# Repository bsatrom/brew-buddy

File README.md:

# Brew Buddy

Source for the BrewBuddy project. Contains sources for board hardware/layout, firmware and a 3d printed enclosure.

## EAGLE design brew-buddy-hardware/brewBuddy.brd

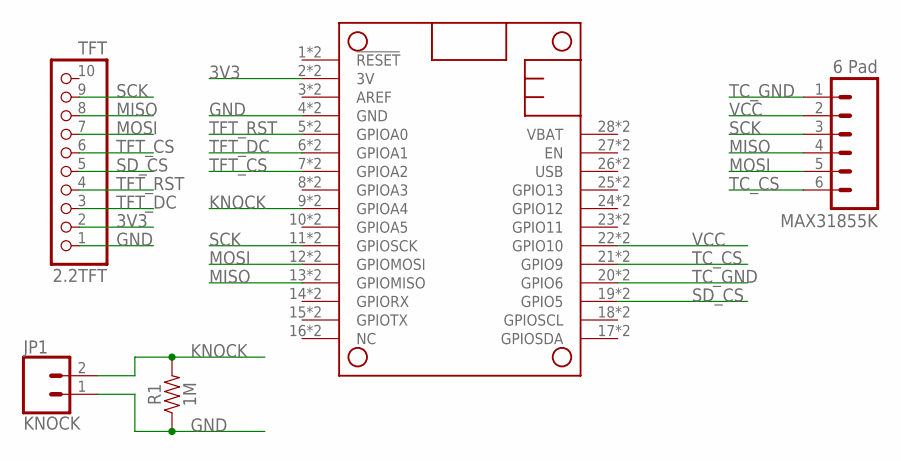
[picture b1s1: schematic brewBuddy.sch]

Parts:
2.2TFT: TFT; MICROBUILDER_1X10_ROUND_2MM
JP1: KNOCK; SCREWTERMINAL-5MM-2
MAX31855K: 6 Pad; 1X06_LONGPADS
MS1: FEATHERWING_SMTDUAL; FEATHERWING_SMT2
R1: 1M; 0805

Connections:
3V3: 2.2TFT.2, MS1.2 (3V), MS1.2' (3V)
GND: 2.2TFT.1, JP1.1, MS1.4 (GND), MS1.4' (GND), R1.1
KNOCK: JP1.2, MS1.9 (GPIOA4), MS1.9' (GPIOA4), R1.2
MISO: 2.2TFT.8, MAX31855K.4, MS1.13 (GPIOMISO), MS1.13' (GPIOMISO)
MOSI: 2.2TFT.7, MAX31855K.5, MS1.12 (GPIOMOSI), MS1.12' (GPIOMOSI)
SCK: 2.2TFT.9, MAX31855K.3, MS1.11 (GPIOSCK), MS1.11' (GPIOSCK)
SD_CS: 2.2TFT.5, MS1.19 (GPIO5), MS1.19' (GPIO5)
TC_CS: MAX31855K.6, MS1.21 (GPIO9), MS1.21' (GPIO9)
TC_GND: MAX31855K.1, MS1.20 (GPIO6), MS1.20' (GPIO6)
TFT_CS: 2.2TFT.6, MS1.7 (GPIOA2), MS1.7' (GPIOA2)
TFT_DC: 2.2TFT.3, MS1.6 (GPIOA1), MS1.6' (GPIOA1)
TFT_RST: 2.2TFT.4, MS1.5 (GPIOA0), MS1.5' (GPIOA0)
VCC: MAX31855K.2, MS1.22 (GPIO10), MS1.22' (GPIO10)

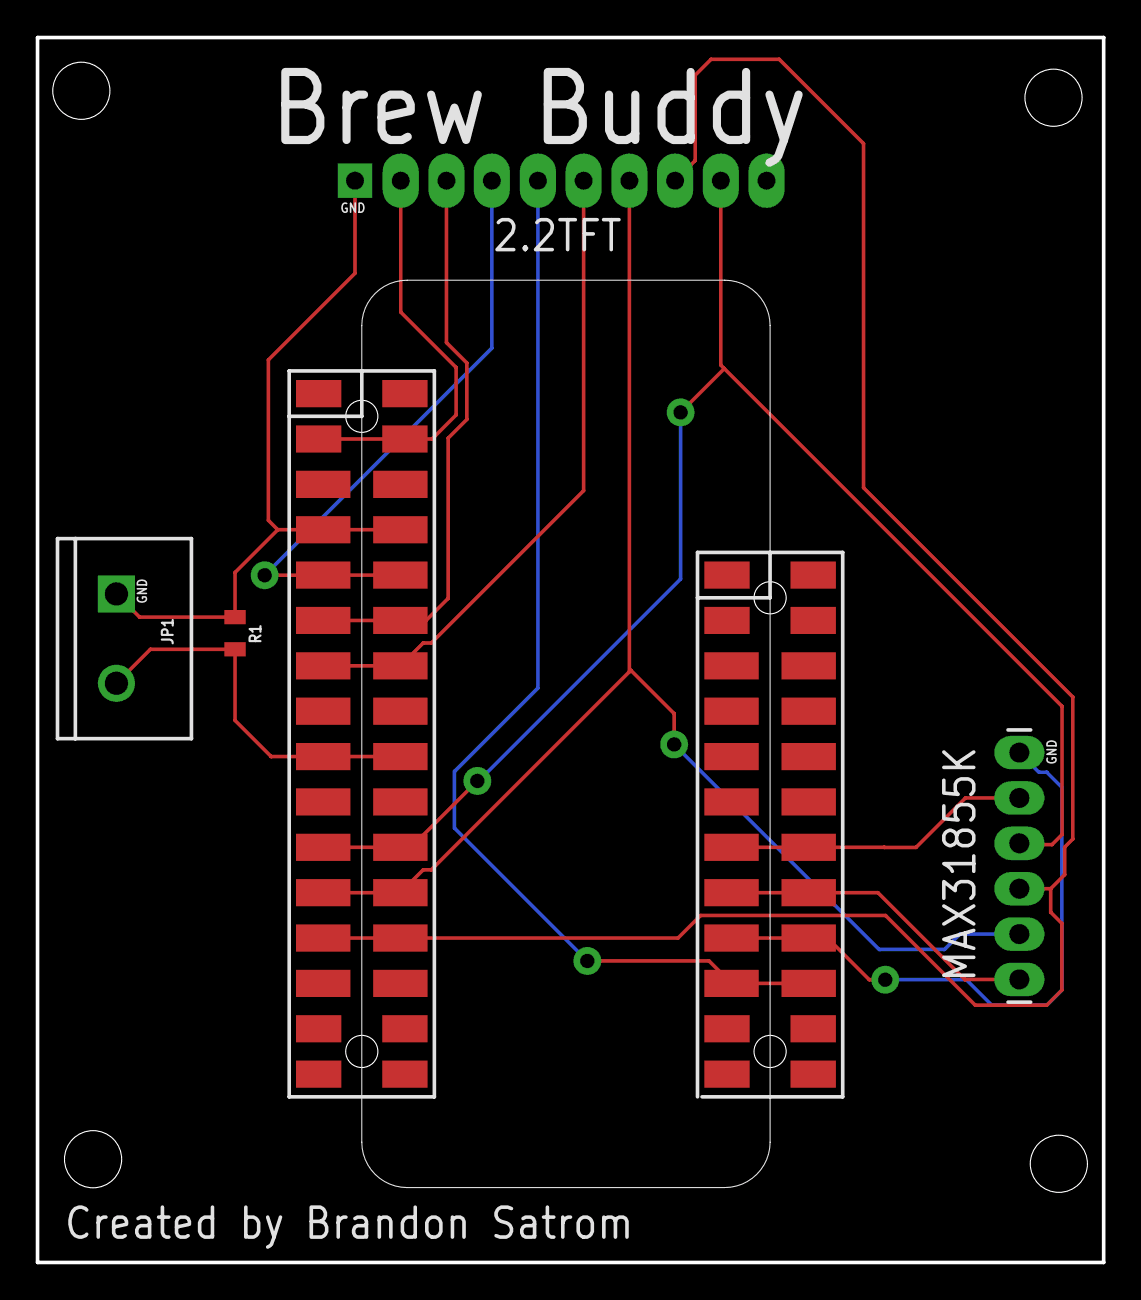
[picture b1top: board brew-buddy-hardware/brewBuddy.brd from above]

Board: 2 copper layers, 59.7 x 68.6 mm, 5 parts (0 on the bottom side), 13 nets.

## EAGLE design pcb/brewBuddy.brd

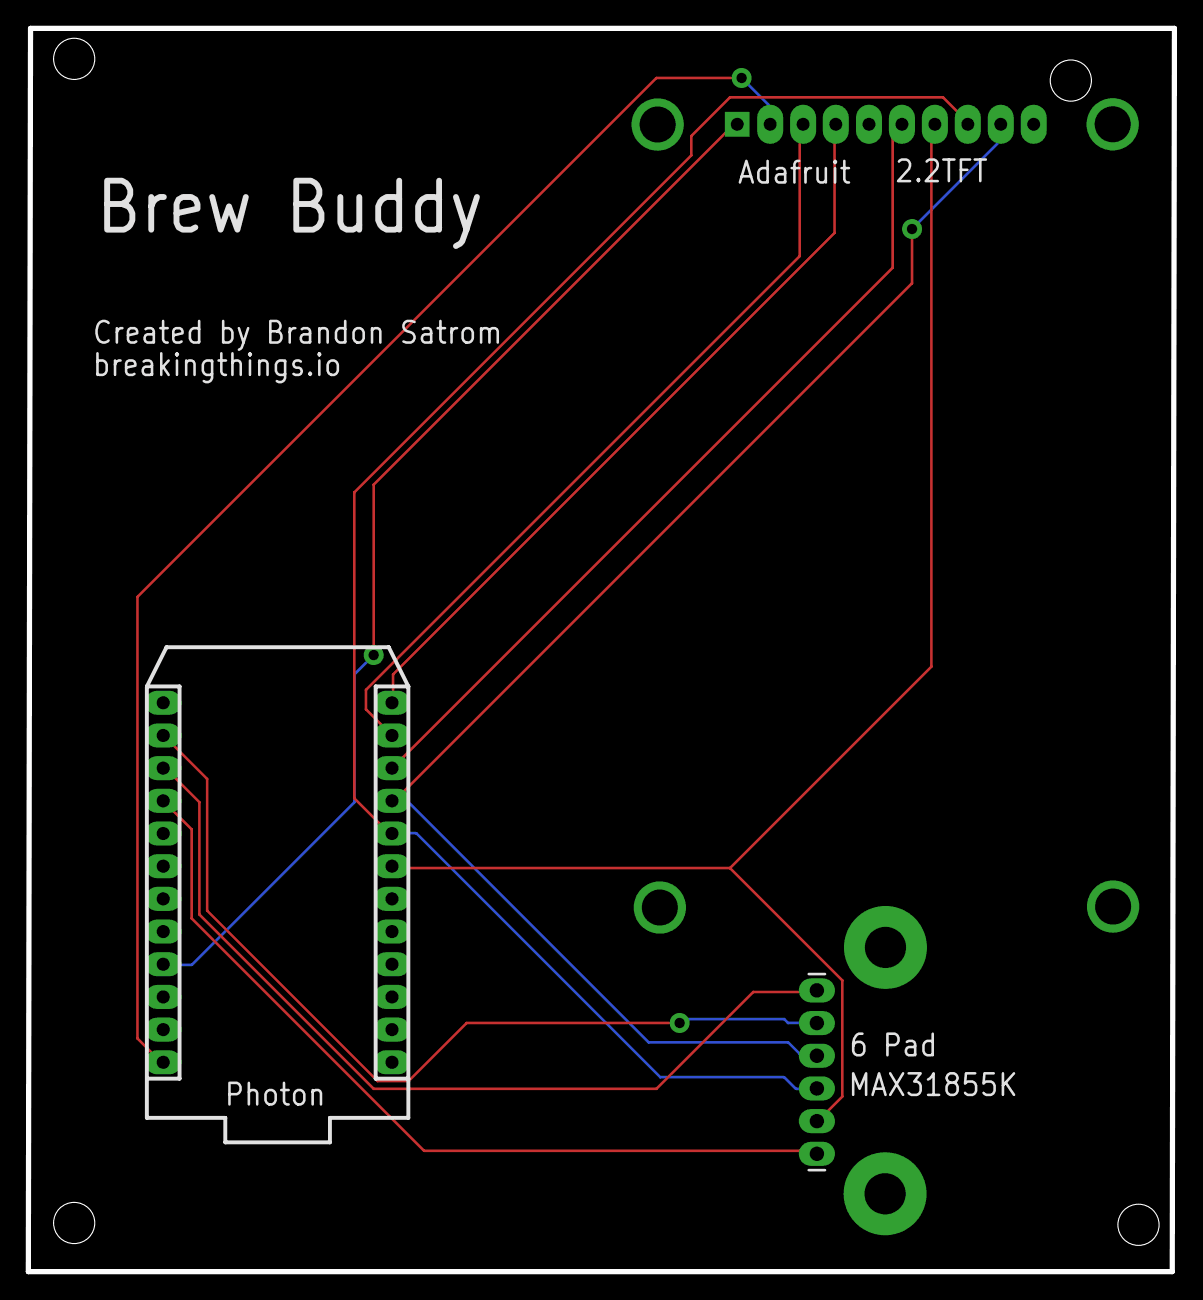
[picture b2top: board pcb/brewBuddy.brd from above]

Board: 2 copper layers, 89.1 x 96.6 mm, 3 parts (0 on the bottom side), 11 nets.

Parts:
2.2TFT: MICROBUILDER_1X10_ROUND_2MM
MAX31855K: 6 Pad; 1X06_LONGPADS
U$1: PHOTON_WITH_HEADERS; PHOTON

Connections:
unnamed: MAX31855K.1, U$1.15
unnamed: MAX31855K.2, U$1.14
unnamed: MAX31855K.6, U$1.16
unnamed: 2.2TFT.9, MAX31855K.3, U$1.9
unnamed: 2.2TFT.8, MAX31855K.4, U$1.8
unnamed: 2.2TFT.7, MAX31855K.5, U$1.7
unnamed: 2.2TFT.6, U$1.10
unnamed: 2.2TFT.4, U$1.12
unnamed: 2.2TFT.3, U$1.11
unnamed: 2.2TFT.2, U$1.24
unnamed: 2.2TFT.1, U$1.21

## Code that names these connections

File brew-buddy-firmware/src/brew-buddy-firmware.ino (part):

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SparkFunMAX31855k probe(CHIP_SELECT_PIN, VCC, GND);

// CS Pin for SD Card on TFT
#define SD_CS D2
#define TFT_CS A2
#define TFT_DC A1
#define TFT_RST A0
// Use hardware SPI
// cs = A2, dc = A1, rst = A0
Adafruit_ILI9341 tft = Adafruit_ILI9341(TFT_CS, TFT_DC, TFT_RST);
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
// #include "bmpDraw.h"

// Knock sensor pin
const uint8_t KNOCK_PIN = A4;

// Timing Variables
unsigned long previousTempMillis = 0;
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  Serial.begin(9600);
  deviceID = System.deviceID();

  pinMode(KNOCK_PIN, INPUT_PULLDOWN);

  //Particle Variables
  Particle.variable("brewStage", brewStage);
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
  if (isFermentationMode)
  {
    int16_t knockVal = analogRead(KNOCK_PIN) / 16;

    if (knockVal >= 6)
    {
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    printSubheadingLine("Waiting for");
    printSubheadingLine("Fermentation...");

    System.sleep(KNOCK_PIN, CHANGE);

    return 1;
  }
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
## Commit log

2016-01-06 resolve .gitignore conflict
2016-01-06 added backend posting and counter on TFT
2016-01-06 added heading text for temp and counter
2016-01-06 Added to Readme
2016-01-06 removed Arduino example/test code
2016-01-07 added temp graph to bottom of TFT
2016-01-21 added Eagle files for brew-buddy PCB
2016-03-17 added Eagle files
2016-07-12 updated brd with larger pads for othermill
2016-07-14 widened wires for cnc millin
2016-07-18 updated brd for othermill
2016-07-20 moved traces to bottom layer for othermill
2016-07-20 added BB name to board
2016-09-06 modified BRD to make room for components
2016-09-07 additional BRD mods
2016-10-27 added enclosure files
2016-10-27 added supports
2016-10-27 updated snclosure with tweaks
2016-10-30 tweaked enclosure (v3)
2016-10-30 additional enclosure tweaks (v4)
2016-10-31 designed top of enclosure
2016-10-31 tweaked top enclosure
2016-11-08 modified sketch to show image on startup; tweaked pcb
2016-11-10 moved WebHook to Firebase; added support for multiple commands in brew creation
2016-11-10 added line to free char memory after processing
2016-11-29 updated enclosure design for smaller case
2016-11-29 added enclosure STL
2016-11-30 modified top of enclosure design
2017-01-08 modified BB firmware to fix a few bugs
2017-01-12 tweaked display settings and location for temp graph
2017-02-13 added basic simulation support
2017-02-13 remove node_modulues
2017-02-13 add node_modulus to `.gitignore`
2017-02-13 cleaned up status changes
2017-02-20 add temp simulator object to control pattern
2017-02-21 cleanup refactor
2019-02-12 re-org and cleanup repo for 2.0 project
2019-02-12 updated library refs; closes #1
2019-02-12 change pin mappings for Argon; closes #2; closes #3
2019-02-20 updated schematic and board for Argon
2019-02-20 completed sd card support; closes #4; closes #5
2019-02-21 overlay text on image for splash; closes #12
2019-02-21 clear screen after startup; closes #16
2019-02-21 up SPI TFT frequency to 120 MHz; closes #11
2019-02-21 implement System threading; closes #17
2019-02-21 added modes for brew and fermentation; closes #8
2019-02-21 calibrate knock sensor; closes #7
2019-02-21 Set up CI with Azure Pipelines
2019-02-21 Update azure-pipelines.yml for Azure Pipelines
2019-02-22 update dependencies for cloud build
2019-02-22 Update azure-pipelines.yml for Azure Pipelines
    Added saveTo command for firmware build
2019-02-22 Update azure-pipelines.yml for Azure Pipelines
    Ad]d GitHub release task
2019-02-22 added brew bitmap
2019-02-22 implemented sleep mode with Knock sensor; closes #10
2019-02-26 added fermentation variables; closes #21
2019-02-26 added fermentation rate logic; closes #23
2019-02-28 separate readings from posting; closes #18; closes #24
2019-02-28 clean-up tempo monitoring posts; closes #22
2019-03-04 display fermentation time; closes #29
2019-03-04 give all pubs a common root; closes #30
2019-03-08 publish temp and fermentation rates; closes #31
2019-03-12 add batt check logic and low batt notification; closes #38; closes #35
2019-03-13 tweak clear screen to leave top bar pixels alone; closes #39
2019-03-13 Add voltage check function and clean up top bar clearing; closes #41
2019-03-13 clean up fermentation display; closes #42
2019-03-14 get MQTT with AzIoT working; for #37
2019-03-16 continue work on Azure IoT Hub integration
2019-03-20 completed c2d message support; closes #37
2019-03-22 change publishing payload for electric-io; closes #45
2019-03-25 implemented filter on fermentation knock detection; closes #36
2019-03-26 fix mqtt message text

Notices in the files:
parts and their libraries:
SparkFun-Resistors: Licensing: Creative Commons ShareAlike 4.0 International - https://creativecommons.org/licenses/by-sa/4.0
